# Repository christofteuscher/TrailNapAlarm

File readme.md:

# Trail Nap Alarm
## Overview

### Introduction and problem statement:
Ultra marathon runners, i.e., runners who run distances longer than a marathon, often do “trail naps,” i.e., they simply lay down on the trail and power nap for 5-10min. When it’s cold, one wakes up after a short period of time, but when it’s warm(er), it’s likely that the runner will sleep longerthan they want. Setting an alarm is tedious, time-consuming, and the alarm may not be heard. Also,sometimes it takes a few minutes to fall asleep, so estimating the wake-up time is hard and the resulting sleep time is rarely ideal.
The goal of this project is to build a device that monitors a runner’s sleep and wakes them up aftersleep stage N1, before they fall into a REM sleep pattern. Non-REM sleep has 3 stages ([Source:](https://www.uofmhealth.org/health-library/hw48331)):
* **Stage** N1 occurs right after you fall asleep and is very short (usually less than 10 minutes).It involves light sleep from which you can be awakened easily.
* **Stage N2** lasts from about 30 to 60 minutes. During this stage, your muscles become more relaxed and you may begin to have slow-wave (delta) brain activity.
* **Stage N3** is deep sleep and lasts about 20 to 40 minutes. During this stage, delta brain activity increases and a person may have some body movements. It is very hard to wake up someone in stage N3.

### Specific project goals
1. Build a sensor system that allows to detect the different sleep patterns. The sensor system needs to be small, simple, non-invasive, and ultra-low power. E.g., an armband, electrodes embedded in a hat, etc.
2. Build a system that reliably wakes up a person. E.g., a combination of sound, vibration, etc. That part must also be small, simple, non-invasive, and ultra-low power.
3. An integration of these two sub-components into a fully functional system. Cables should be avoided. If communication between sub-systems is necessary, that should rely on Bluetooth or other protocols.
4. The system must be battery-powered. The batteries should last for at least 3 days (72 hours). The batteries should be rechargeable with a USB cable.
5. The overall system must be small, non-invasive, light, water-proof, easy to use, and have no on-off or other switches.

## Project status
This project is unfinished and serves only as a proof-of-concept. The intention is for the final product to be as passively-operational as possible - meaning that all the user has to do is turn it on and wear it during a nap, then turn it off when they are woken up. For further development, please refer to the [documentation in the wiki for this repository](https://github.com/cteusche/TrailNapAlarm/wiki).

To start developing this project:
1. Clone this repository
2. Install [conda mini-forge](https://github.com/conda-forge/miniforge) package handler.
3. In the terminal, go to the home directory of this repo and run the command 
   
   `conda env create -f environment.yml` 
   
   to set up a new conda environment and install the required python libraries into it.

## Directory structure
* [src](https://github.com/cteusche/TrailNapAlarm/tree/main/src)
    * Source code files belong here
* [tools](https://github.com/cteusche/TrailNapAlarm/tree/main/tools)
    * Tools like Makefile and other scripts belong here
* [docs](https://github.com/cteusche/TrailNapAlarm/tree/main/docs)
    * Documentation files belong here
* [dep](https://github.com/cteusche/TrailNapAlarm/tree/main/dep)
    * Dependencies belong here
* [res](https://github.com/cteusche/TrailNapAlarm/tree/main/res)
    * Resource files belong here

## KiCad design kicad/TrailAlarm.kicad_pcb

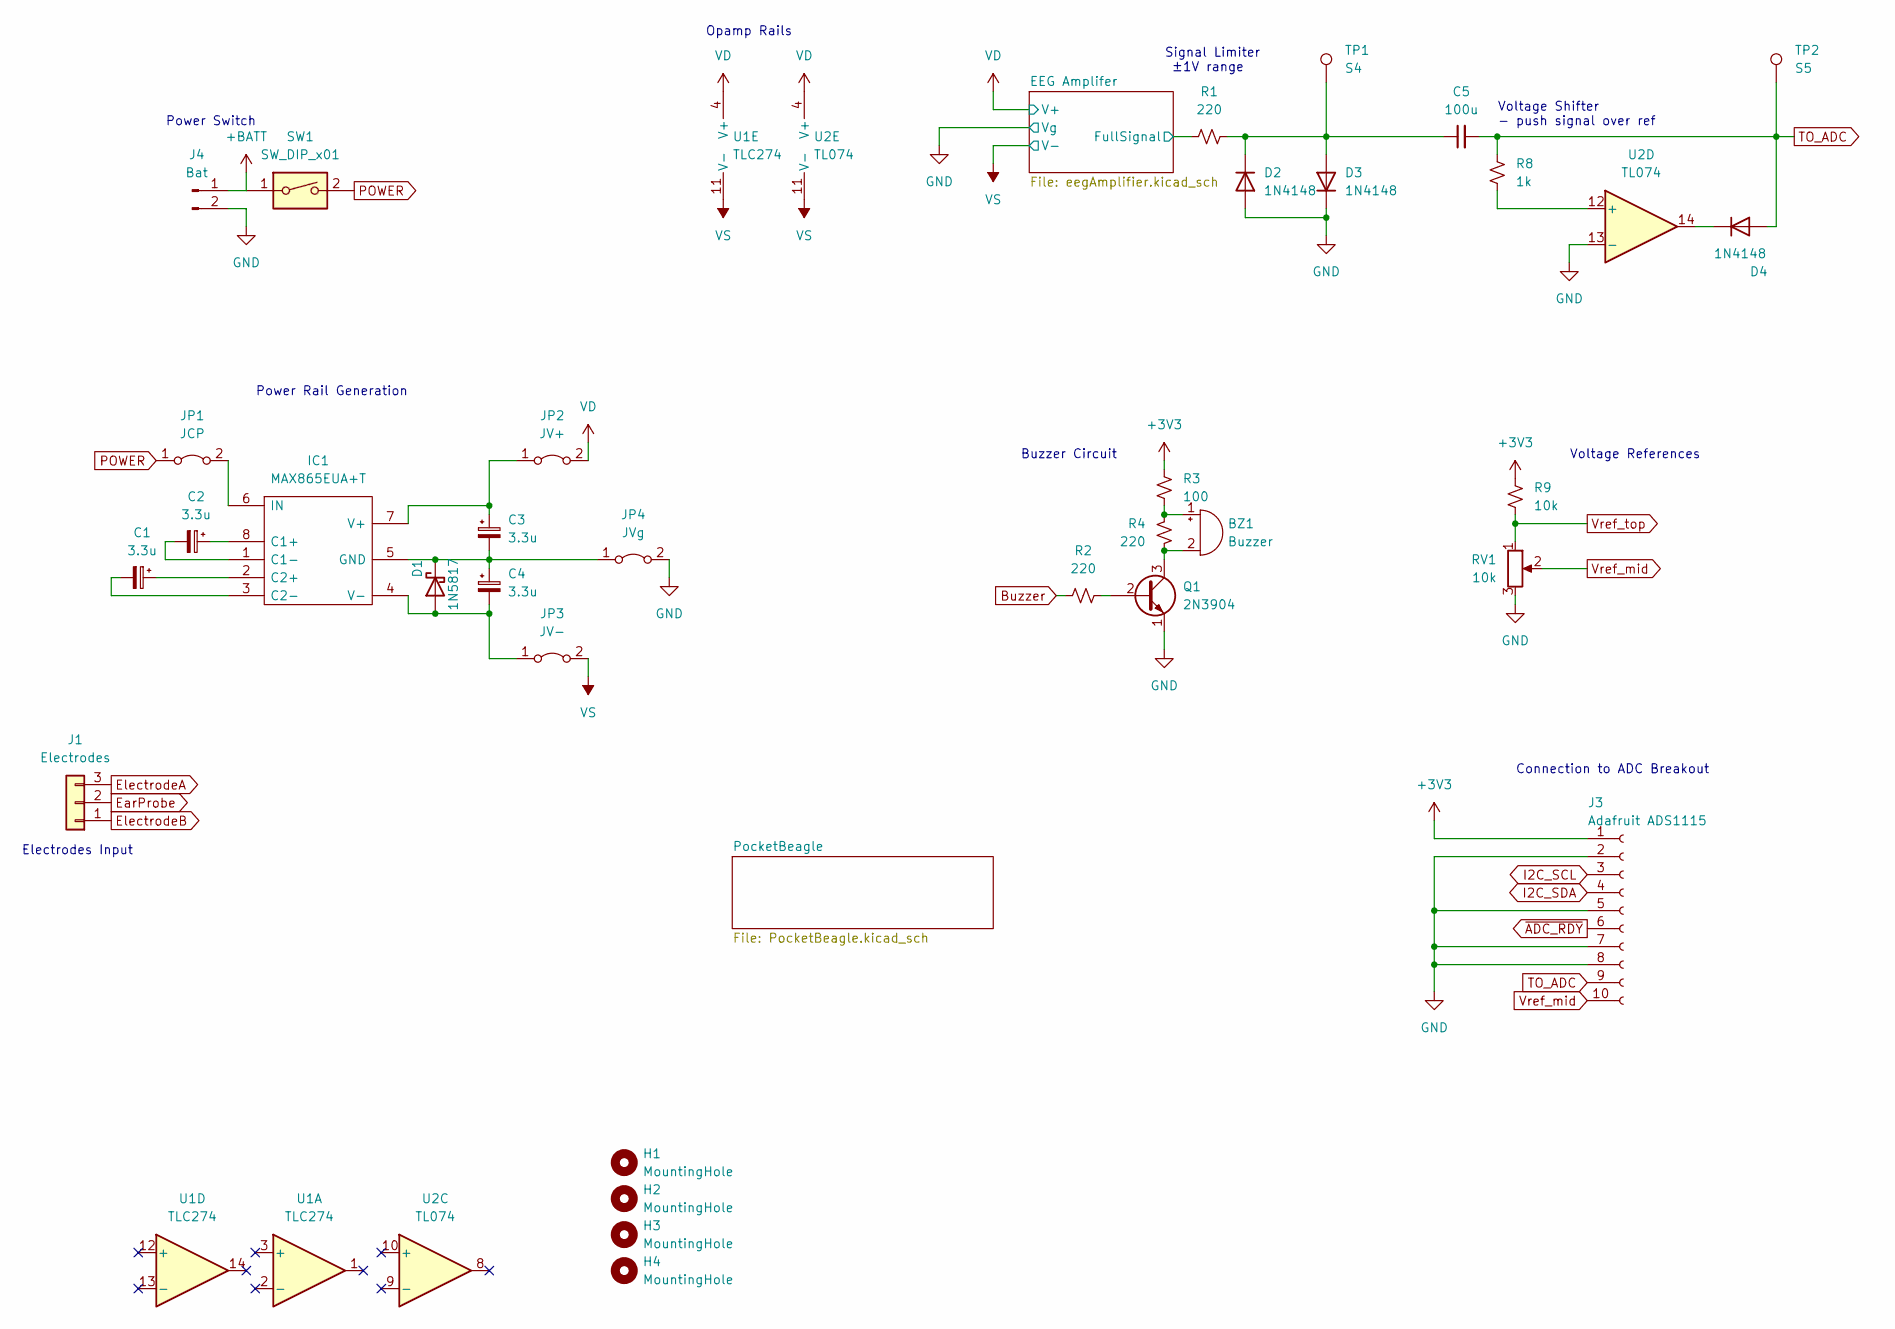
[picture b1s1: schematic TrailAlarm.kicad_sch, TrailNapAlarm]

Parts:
BZ1: Buzzer; Buzzer_12x9.5RM7.6
C1, C2, C3, C4: 3.3u; CP_Radial_D4.0mm_P1.50mm
C5: 100u; C_Radial_D5.0mm_H7.0mm_P2.00mm
D1: 1N5817; D_DO-41_SOD81_P10.16mm_Horizontal
D2, D3, D4: 1N4148; D_DO-35_SOD27_P5.08mm_Vertical_AnodeUp
H1, H2, H3, H4: MountingHole; MountingHole_2.2mm_M2
IC1: MAX865EUA+T; SOP65P490X111-8N; Mouser Part Number 700-MAX865EUAT
J1: Electrodes; PinHeader_1x03_P2.54mm_Horizontal
J3: Adafruit ADS1115; PinHeader_1x10_P2.54mm_Vertical
J4: Bat; PinHeader_1x02_P2.54mm_Vertical
JP1: JCP; TestPoint_2Pads_Pitch2.54mm_Drill0.8mm
JP2: JV+; TestPoint_2Pads_Pitch2.54mm_Drill0.8mm
JP3: JV-; TestPoint_2Pads_Pitch2.54mm_Drill0.8mm
JP4: JVg; TestPoint_2Pads_Pitch2.54mm_Drill0.8mm
Q1: 2N3904; TO-92_Inline
R1, R2, R4: 220; R_1206_3216Metric_Pad1.30x1.75mm_HandSolder
R3: 100; R_1206_3216Metric_Pad1.30x1.75mm_HandSolder
R8: 1k; R_1206_3216Metric_Pad1.30x1.75mm_HandSolder
R9: 10k; R_1206_3216Metric_Pad1.30x1.75mm_HandSolder
RV1: 10k; Potentiometer_Bourns_3266Y_Vertical
SW1: SW_DIP_x01; SW_CuK_JS202011AQN_DPDT_Angled
TP1: S4; TestPoint_Pad_D1.0mm
TP2: S5; TestPoint_Pad_D1.0mm
U1: TLC274; DIP-14_W7.62mm_LongPads
U2: TL074; DIP-14_W7.62mm_LongPads

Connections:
+3V3: J3.1, R3.1, R9.1; also elsewhere on the board
+BATT: J4.1, SW1.1
/EEG Amplifer/FullSignal: R1.1; also elsewhere on the board
Buzzer: R2.1; also elsewhere on the board
EarProbe: J1.2; also elsewhere on the board
ElectrodeA: J1.3; also elsewhere on the board
ElectrodeB: J1.1; also elsewhere on the board
I2C_SCL: J3.3; also elsewhere on the board
I2C_SDA: J3.4; also elsewhere on the board
unnamed: BZ1.1 (-), R3.2, R4.2
unnamed: BZ1.2 (+), Q1.3 (C), R4.1
unnamed: C1.1, IC1.2 (C2+)
unnamed: C1.2, IC1.3 (C2-)
unnamed: C2.1, IC1.8 (C1+)
unnamed: C2.2, IC1.1 (C1-)
unnamed: C3.1, IC1.7 (V+), JP2.1 (A)
unnamed: C3.2, C4.1, D1.1 (K), IC1.5 (GND), JP4.1 (A)
unnamed: C4.2, D1.2 (A), IC1.4 (V-), JP3.1 (A)
unnamed: C5.1, D2.1 (K), D3.2 (A), R1.2, TP1.1
unnamed: D4.1 (K), U2.14
unnamed: IC1.6 (IN), JP1.2 (B)
unnamed: Q1.2 (B), R2.2
unnamed: R8.2, U2.12 (+)
POWER: JP1.1 (A), SW1.2; also elsewhere on the board
TO_ADC: C5.2, D4.2 (A), J3.9, R8.1, TP2.1
VD: JP2.2 (B), U1.4 (V+), U2.4 (V+); also elsewhere on the board
VS: JP3.2 (B), U1.11 (V-), U2.11 (V-); also elsewhere on the board
Vref_mid: J3.10, RV1.2
Vref_top: R9.2, RV1.1
~ADC_RDY: J3.6; also elsewhere on the board

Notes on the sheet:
Electrodes Input
Voltage References
Signal Limiter ±1V range
Voltage Shifter - push signal over ref
Buzzer Circuit
Connection to ADC Breakout
Power Switch
Opamp Rails
Power Rail Generation

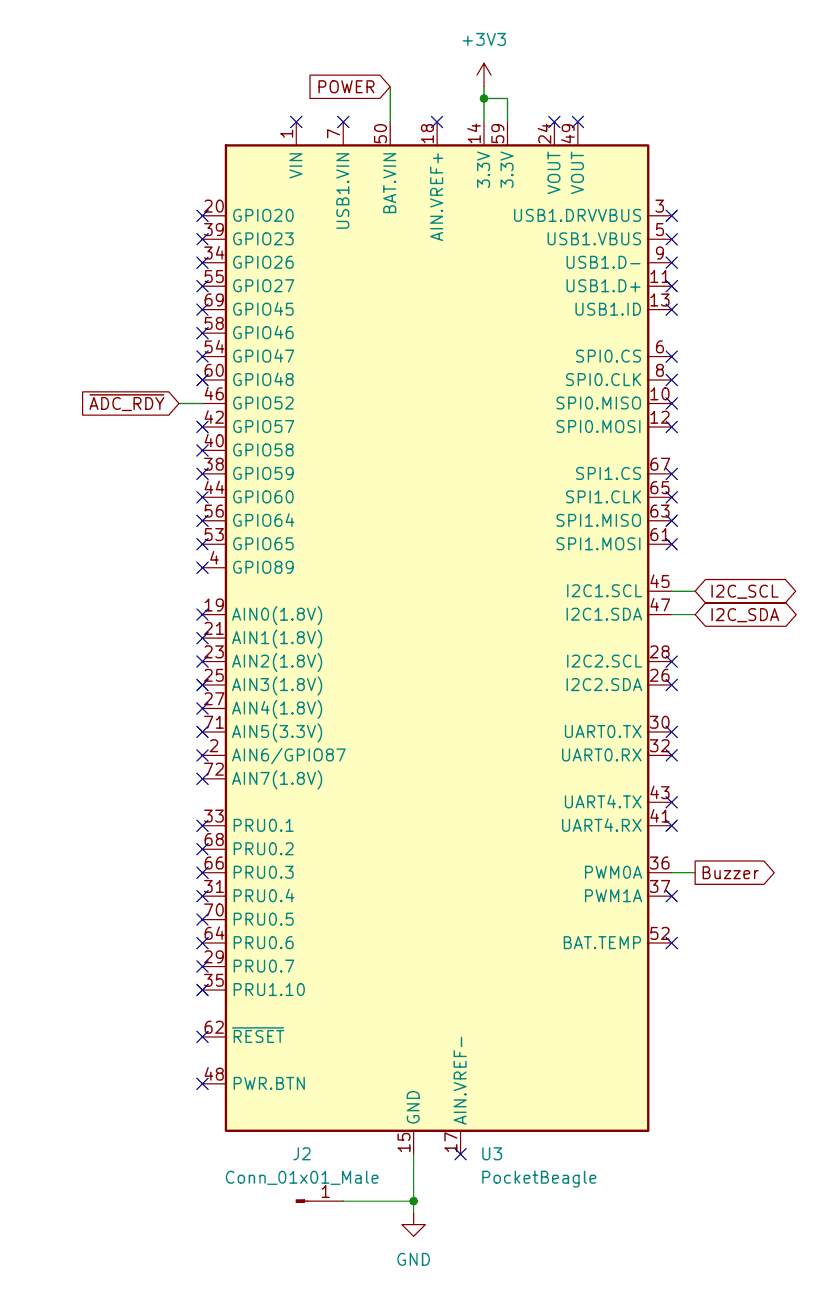
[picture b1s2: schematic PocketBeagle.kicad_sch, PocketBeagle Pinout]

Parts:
J2: Conn_01x01_Male; PinHeader_1x01_P2.54mm_Vertical
U3: PocketBeagle; BeagleBoard_PocketBeagle

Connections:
+3V3: U3.14 (3.3V), U3.59 (3.3V); also elsewhere on the board
Buzzer: U3.36 (PWM0A); also elsewhere on the board
I2C_SCL: U3.45 (I2C1.SCL); also elsewhere on the board
I2C_SDA: U3.47 (I2C1.SDA); also elsewhere on the board
POWER: U3.50 (BAT.VIN); also elsewhere on the board
~ADC_RDY: U3.46 (GPIO52); also elsewhere on the board

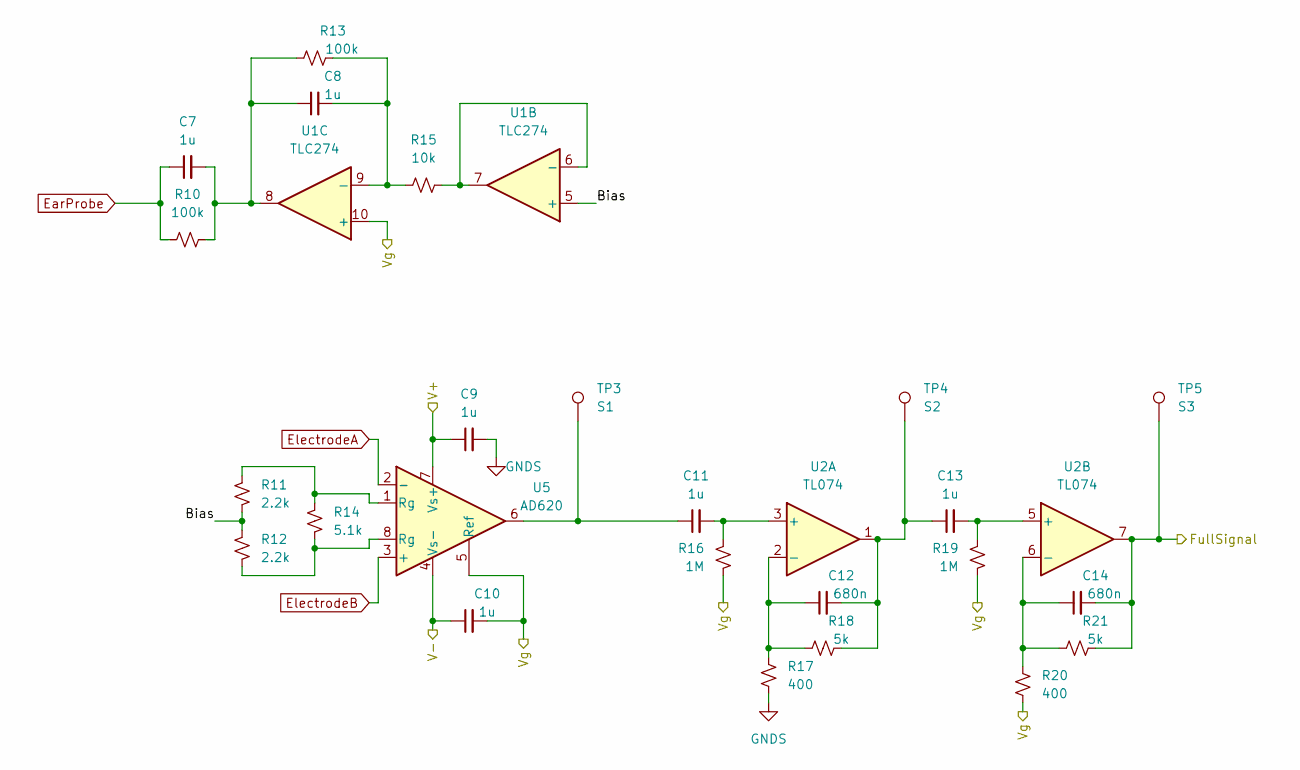
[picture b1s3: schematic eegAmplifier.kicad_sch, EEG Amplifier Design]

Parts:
C7, C8, C9, C10, C11, C13: 1u; C_0805_2012Metric_Pad1.18x1.45mm_HandSolder
C12, C14: 680n; C_Disc_D3.8mm_W2.6mm_P2.50mm
R10, R13: 100k; R_1206_3216Metric_Pad1.30x1.75mm_HandSolder
R11, R12: 2.2k; R_1206_3216Metric_Pad1.30x1.75mm_HandSolder
R14: 5.1k; R_1206_3216Metric_Pad1.30x1.75mm_HandSolder
R15: 10k; R_1206_3216Metric_Pad1.30x1.75mm_HandSolder
R16, R19: 1M; R_1206_3216Metric_Pad1.30x1.75mm_HandSolder
R17, R20: 400; R_1206_3216Metric_Pad1.30x1.75mm_HandSolder
R18, R21: 5k; R_1206_3216Metric_Pad1.30x1.75mm_HandSolder
TP3: S1; TestPoint_Pad_D1.0mm
TP4: S2; TestPoint_Pad_D1.0mm
TP5: S3; TestPoint_Pad_D1.0mm
U1: TLC274; DIP-14_W7.62mm_LongPads
U2: TL074; DIP-14_W7.62mm_LongPads
U5: AD620; DIP-8_W7.62mm_LongPads

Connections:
/EEG Amplifer/Bias: R11.2, R12.1, U1.5 (+)
/EEG Amplifer/FullSignal: C14.2, R21.2, TP5.1, U2.7; also elsewhere on the board
EarProbe: C7.1, R10.1; also elsewhere on the board
ElectrodeA: U5.2 (-); also elsewhere on the board
ElectrodeB: U5.3 (+); also elsewhere on the board
unnamed: C7.2, C8.1, R10.2, R13.1, U1.8
unnamed: C8.2, R13.2, R15.1, U1.9 (-)
unnamed: C11.1, TP3.1, U5.6
unnamed: C11.2, R16.2, U2.3 (+)
unnamed: C12.1, R17.1, R18.1, U2.2 (-)
unnamed: C12.2, C13.1, R18.2, TP4.1, U2.1
unnamed: C13.2, R19.2, U2.5 (+)
unnamed: C14.1, R20.1, R21.1, U2.6 (-)
unnamed: R11.1, R14.1, U5.1 (Rg)
unnamed: R12.2, R14.2, U5.8 (Rg)
unnamed: R15.2, U1.6 (-), U1.7
VD: C9.1, U5.7 (Vs+); also elsewhere on the board
VS: C10.1, U5.4 (Vs-); also elsewhere on the board

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
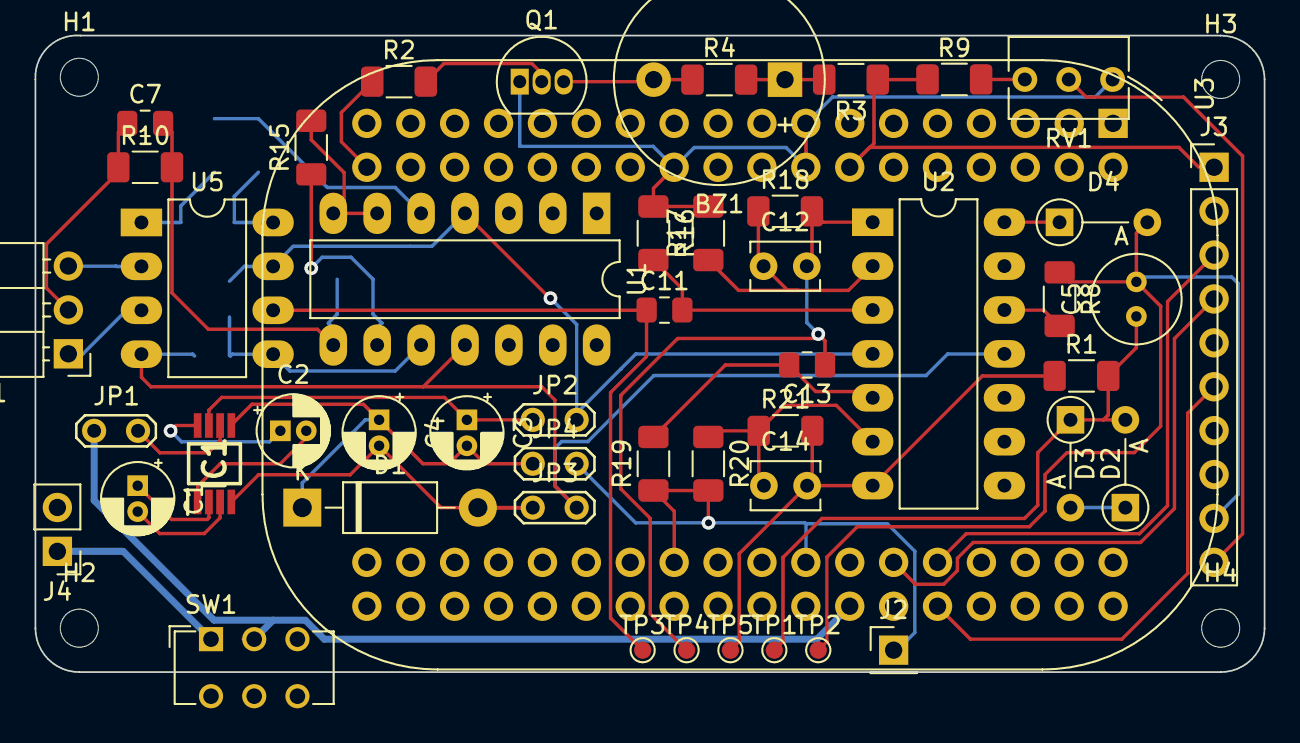
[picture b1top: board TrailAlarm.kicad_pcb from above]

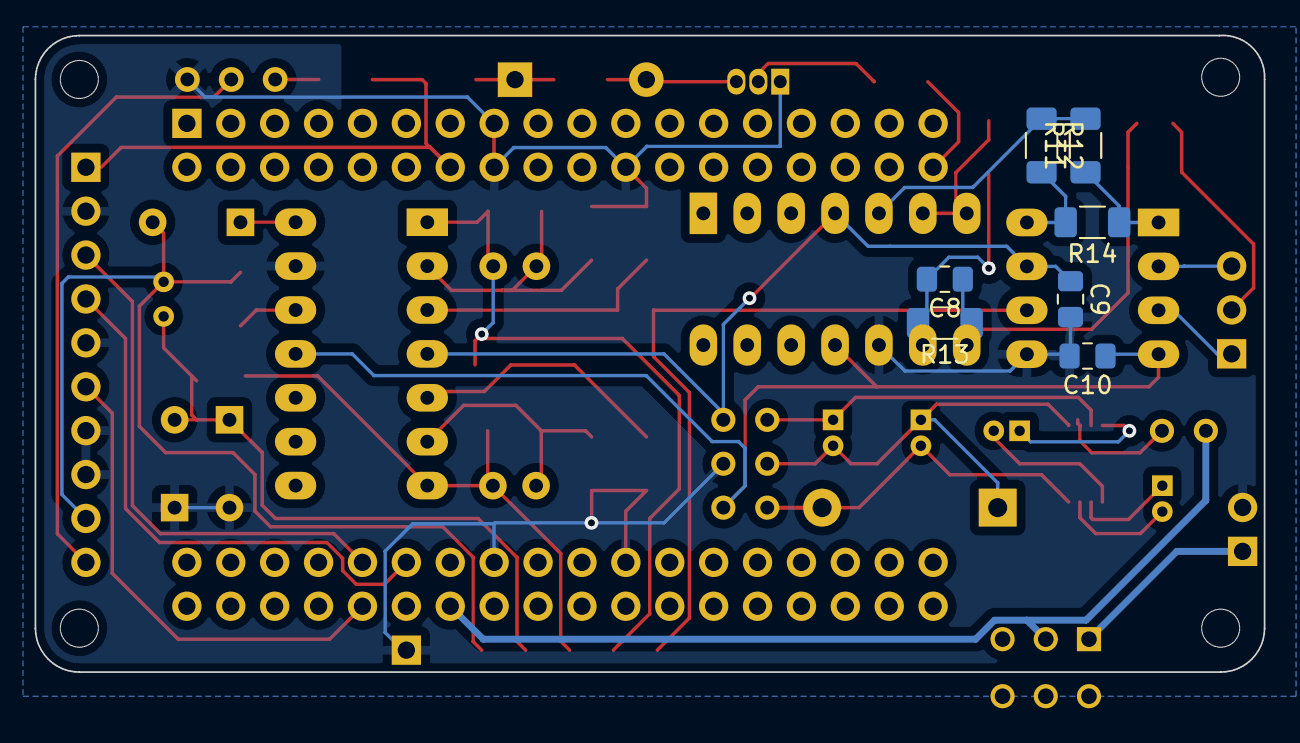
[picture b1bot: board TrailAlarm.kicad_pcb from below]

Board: 2 copper layers, 71.1 x 36.8 mm, 61 parts (7 on the bottom side), 43 nets.

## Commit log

2022-01-11 created a couple folders and started a readme.md
2022-01-11 trying to add directories
2022-01-11 Adding some directories by adding temp files
2022-01-11 corrected spelling error
2022-03-23 Create research
2022-03-27 added viz program to test yasa datasets
2022-03-27 modified file structure
2022-03-27 testing gitignore
2022-03-27 added python requirements list
2022-03-28 added citation
2022-04-06 added test functions for sleep stage prediction
2022-04-06 tested auto sleep scoring function on sample data
2022-05-22 Create pollData.py
    New file for polling data via the ADS1115
2022-05-29 Add files from working sampling
2022-05-30 added image to readme
2022-05-30 added block diagram
2022-05-30 added schematic
2022-05-31 cleanup analysis files and data
2022-05-31 changed gitignore
2022-05-31 Rename collectData2.py to collectData_0.2.py
2022-05-31 Rename collectData.py to collectData_0.1.py
2022-05-31 Rename datasetup.py to dataSetup.py
2022-05-31 Add record.py to gather sampled data into wav
2022-05-31 Added sample python code for handling python
2022-06-01 updated analysis tools
2022-06-01 updated directories
2022-06-01 Add scope setup and screenshots
2022-06-01 updated analysis programs
2022-06-01 replaced image
2022-06-01 modified prediction output
2022-06-02 added wakeup conditions
2022-06-03 updated block diag
2022-06-03 replaced image, added test fcn
2022-06-03 updated test functions
2022-06-04 analysis adjustments
2022-06-04 added conda environment.yml
2022-06-04 updated dependencies
2022-06-05 updated analysis
2022-06-05 added figure
2022-06-05 little adjustments
2022-06-05 added deps txt
2022-06-05 added figures
2022-06-06 added default wake condition
2022-06-06 Modify analysis.py for python<3.10, test input
2022-06-06 Revert "Modify analysis.py for python<3.10, test input"
    This reverts commit d812169c43bd7700fd1704d3e1cf5ce712660c43.
2022-06-06 added sleep recordings
2022-06-08 updated src/readme
2022-06-08 updated src/readme file
2022-06-09 Add jumpers to power rails
2022-06-09 Pin assignment, electrode headers
2022-06-09 Add KiCad Breadboard design
2022-06-09 Added charge pump to generate rails, switch
2022-06-09 Change buzzer pin, i2c pins, ADC plugin, ground pin.
    - Change buzzer PWM pin for easier routing.
    - Use i2c1 on P2_9(SCL) and P2_11(SDA)
    - Use ADS1115 breakout board via header
    - Add ground pin next to test points.
    - Add header for battery.
2022-06-09 Layout finished except test points
2022-06-09 Done footprint assignment
2022-06-09 Done Layout
    - Add paths for test points, better ground plane
2022-06-09 Updated schematic labels, PocketBeagle to separate sheet
2022-06-09 Export gerber files
    - Reflow
    - print to pdf
    - generate gerber/drill files for fab
2022-06-09 organized research docs
2022-06-09 remove empty folder
2022-06-09 Update src directory documentation
2022-06-10 Update src README, add source files from device
2022-06-10 Correct stopping of buzzing
2022-06-10 Added setup files.
2022-06-10 Add info on attempts to setup YASA
2022-06-10 Update links to libraries
2022-06-10 Add ltspice libraries and files
2022-06-10 Update formatting of setup readme
2022-06-10 renamed files
2022-06-10 cleaned up directories
2022-06-10 added datasheets
2022-06-10 Updated layout
2022-06-10 Create readme.md
    Added links
